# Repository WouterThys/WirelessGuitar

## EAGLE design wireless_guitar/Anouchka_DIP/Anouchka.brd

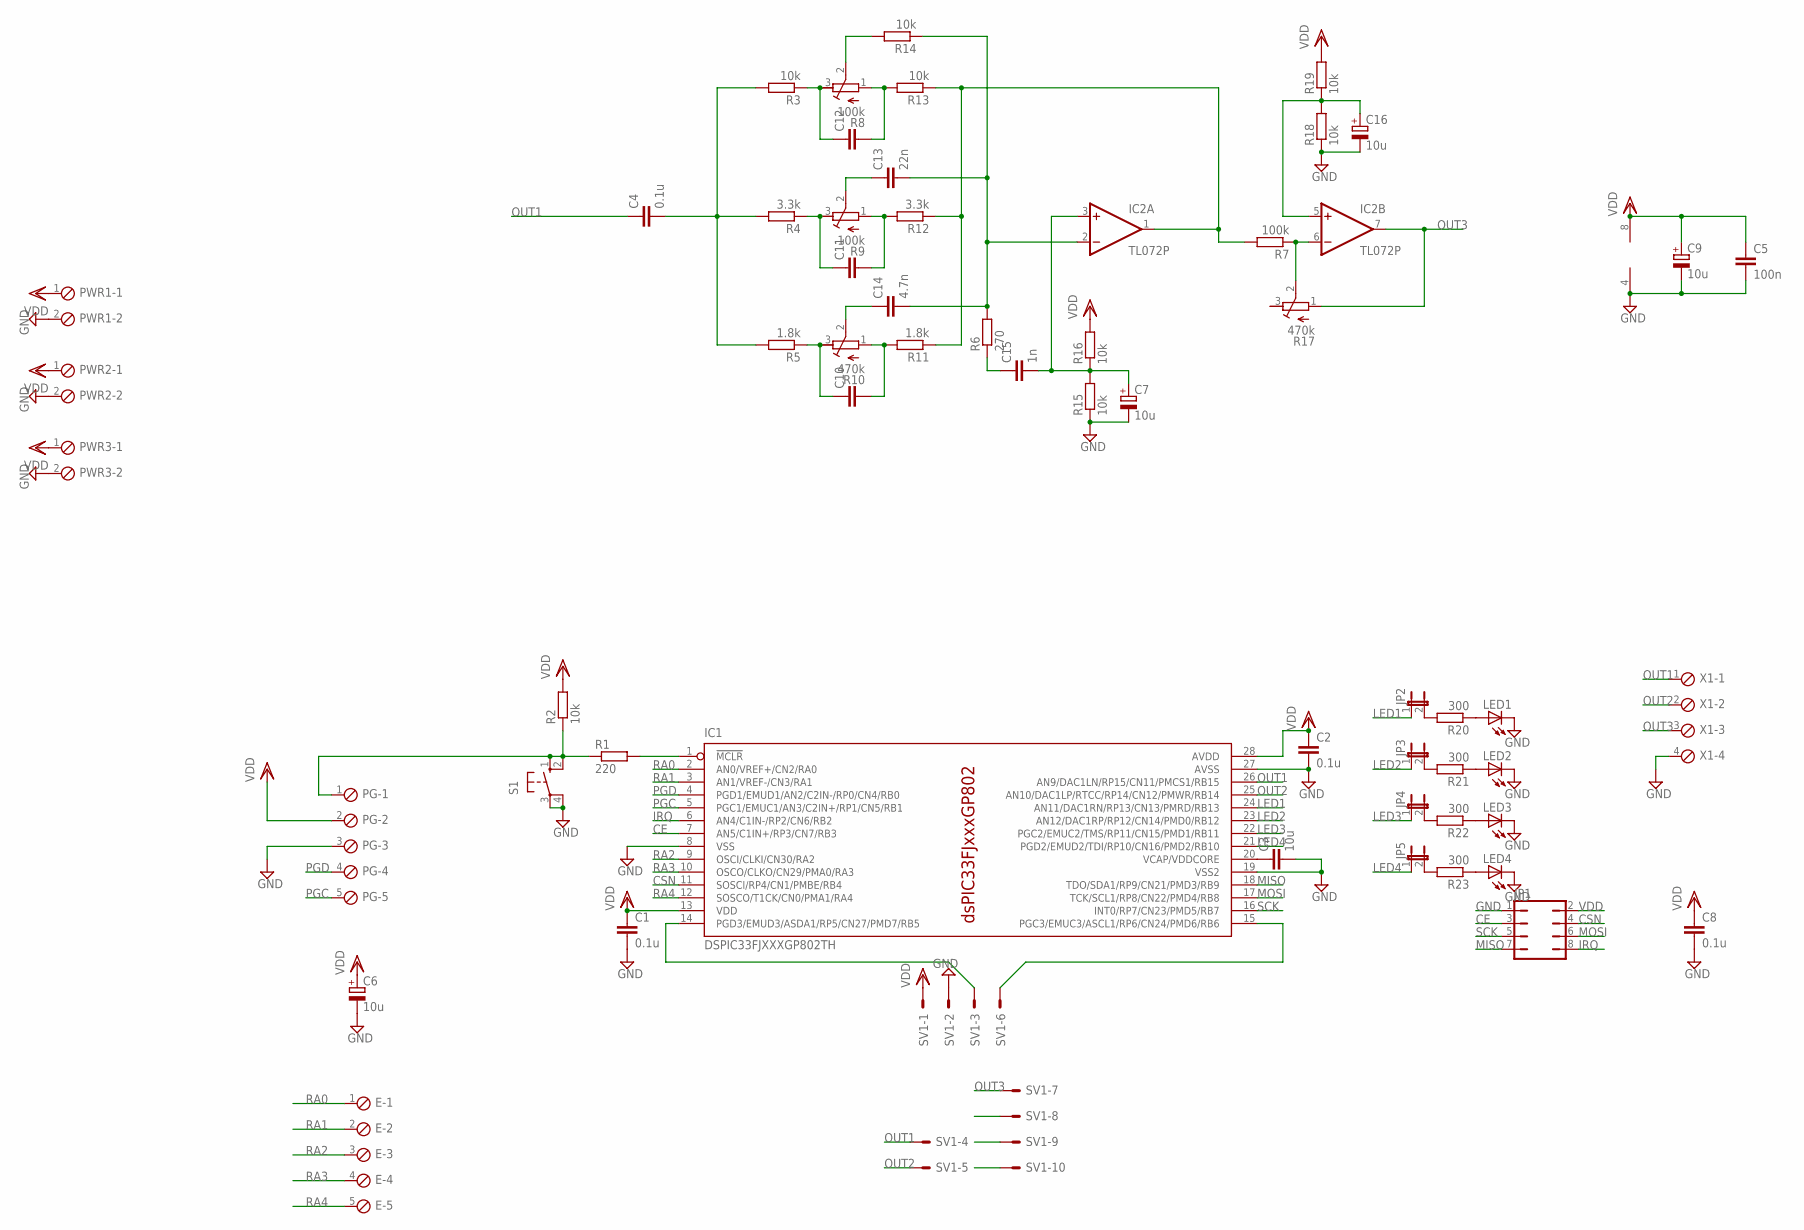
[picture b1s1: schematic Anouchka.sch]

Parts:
C1, C2, C4, C8: 0.1u; C025-024X044
C3: 10u; C025-024X044
C5: 100n; C025-024X044
C6, C7, C9, C16: 10u; E2,5-5
C10, C11, C12: C-EU025-024X044; C025-024X044
C13: 22n; C025-024X044
C14: 4.7n; C025-024X044
C15: 1n; C025-024X044
E: MPT5; 5POL254
IC1: DSPIC33FJXXXGP802TH; DIL28-3
IC2: TL072P; DIL08
JP1: JP4Q
JP2, JP3, JP4, JP5: JP1E; JP1
LED1, LED2, LED3, LED4: LED3MM
PG: MPT5; 5POL254
PWR1, PWR2, PWR3: MPT2; 2POL254
R1: 220; 0207/10
R2, R3, R13, R14, R15, R16, R18, R19: 10k; 0207/10
R4, R12: 3.3k; 0207/10
R5, R11: 1.8k; 0207/10
R6: 270; 0207/10
R7: 100k; 0207/10
R8, R9: 100k; RTRIM3339P
R10, R17: 470k; RTRIM3339P
R20, R21, R22, R23: 300; 0207/10
S1: 10-XX; B3F-10XX
SV1: ML10E; ML10
X1: MPT4; 4POL254

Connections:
CE: IC1.7 (AN5/C1IN+/RP3/CN7/RB3), JP1.3
CSN: IC1.11 (SOSCI/RP4/CN1/PMBE/RB4), JP1.4
GND: C1.2, C2.2, C3.2, C5.2, C6.-, C7.-, C8.2, C9.-, C16.-, IC1.8 (VSS), IC1.19 (VSS2), IC1.27 (AVSS), IC2.4 (V-), JP1.1, LED1.K (C), LED2.K (C), LED3.K (C), LED4.K (C), PG.3, PWR1.2, PWR2.2, PWR3.2, R15.1, R18.1, S1.3, S1.4 (P1), SV1.2, X1.4
IRQ: IC1.6 (AN4/C1IN-/RP2/CN6/RB2), JP1.8
LED1: IC1.24 (AN11/DAC1RN/RP13/CN13/PMRD/RB13), JP2.1
LED2: IC1.23 (AN12/DAC1RP/RP12/CN14/PMD0/RB12), JP3.1
LED3: IC1.22 (PGC2/EMUC2/TMS/RP11/CN15/PMD1/RB11), JP4.1
LED4: IC1.21 (PGD2/EMUD2/TDI/RP10/CN16/PMD2/RB10), JP5.1
MISO: IC1.18 (TDO/SDA1/RP9/CN21/PMD3/RB9), JP1.7
MOSI: IC1.17 (TCK/SCL1/RP8/CN22/PMD4/RB8), JP1.6
unnamed: IC1.1 (!MCLR), R1.2
unnamed: PG.1, R1.1, R2.1, S1.1 (S), S1.2 (S1)
unnamed: C3.1, IC1.20 (VCAP/VDDCORE)
unnamed: IC2.1 (OUT), R7.2, R11.1, R12.1, R13.1
unnamed: C4.2, R3.2, R4.2, R5.2
unnamed: C12.1, R3.1, R8.3 (E)
unnamed: C12.2, R8.1 (A), R13.2
unnamed: C11.1, R4.1, R9.3 (E)
unnamed: C11.2, R9.1 (A), R12.2
unnamed: C10.1, R5.1, R10.3 (E)
unnamed: C10.2, R10.1 (A), R11.2
unnamed: C14.1, R10.2 (S)
unnamed: C13.1, R9.2 (S)
unnamed: R8.2 (S), R14.2
unnamed: C13.2, C14.2, IC2.2 (-IN), R6.2, R14.1
unnamed: C15.1, R6.1
unnamed: IC2.6 (-IN), R7.1, R17.2 (S)
unnamed: C7.+, C15.2, IC2.3 (+IN), R15.2, R16.1
unnamed: C16.+, IC2.5 (+IN), R18.2, R19.1
unnamed: IC1.15 (PGC3/EMUC3/ASCL1/RP6/CN24/PMD6/RB6), SV1.6
unnamed: IC1.14 (PGD3/EMUD3/ASDA1/RP5/CN27/PMD7/RB5), SV1.3
unnamed: JP2.2, R20.2
unnamed: JP3.2, R21.2
unnamed: JP4.2, R22.2
unnamed: JP5.2, R23.2
unnamed: LED1.A, R20.1
unnamed: LED2.A, R21.1
unnamed: LED3.A, R22.1
unnamed: LED4.A, R23.1
OUT1: C4.1, IC1.26 (AN9/DAC1LN/RP15/CN11/PMCS1/RB15), SV1.4, X1.1
OUT2: IC1.25 (AN10/DAC1LP/RTCC/RP14/CN12/PMWR/RB14), SV1.5, X1.2
OUT3: IC2.7 (OUT), R17.1 (A), SV1.7, X1.3
PGC: IC1.5 (PGC1/EMUC1/AN3/C2IN+/RP1/CN5/RB1), PG.5
PGD: IC1.4 (PGD1/EMUD1/AN2/C2IN-/RP0/CN4/RB0), PG.4
RA0: E.1, IC1.2 (AN0/VREF+/CN2/RA0)
RA1: E.2, IC1.3 (AN1/VREF-/CN3/RA1)
RA2: E.3, IC1.9 (OSCI/CLKI/CN30/RA2)
RA3: E.4, IC1.10 (OSCO/CLKO/CN29/PMA0/RA3)
RA4: E.5, IC1.12 (SOSCO/T1CK/CN0/PMA1/RA4)
SCK: IC1.16 (INT0/RP7/CN23/PMD5/RB7), JP1.5
VDD: C1.1, C2.1, C5.1, C6.+, C8.1, C9.+, IC1.13 (VDD), IC1.28 (AVDD), IC2.8 (V+), JP1.2, PG.2, PWR1.1, PWR2.1, PWR3.1, R2.2, R16.2, R19.2, SV1.1

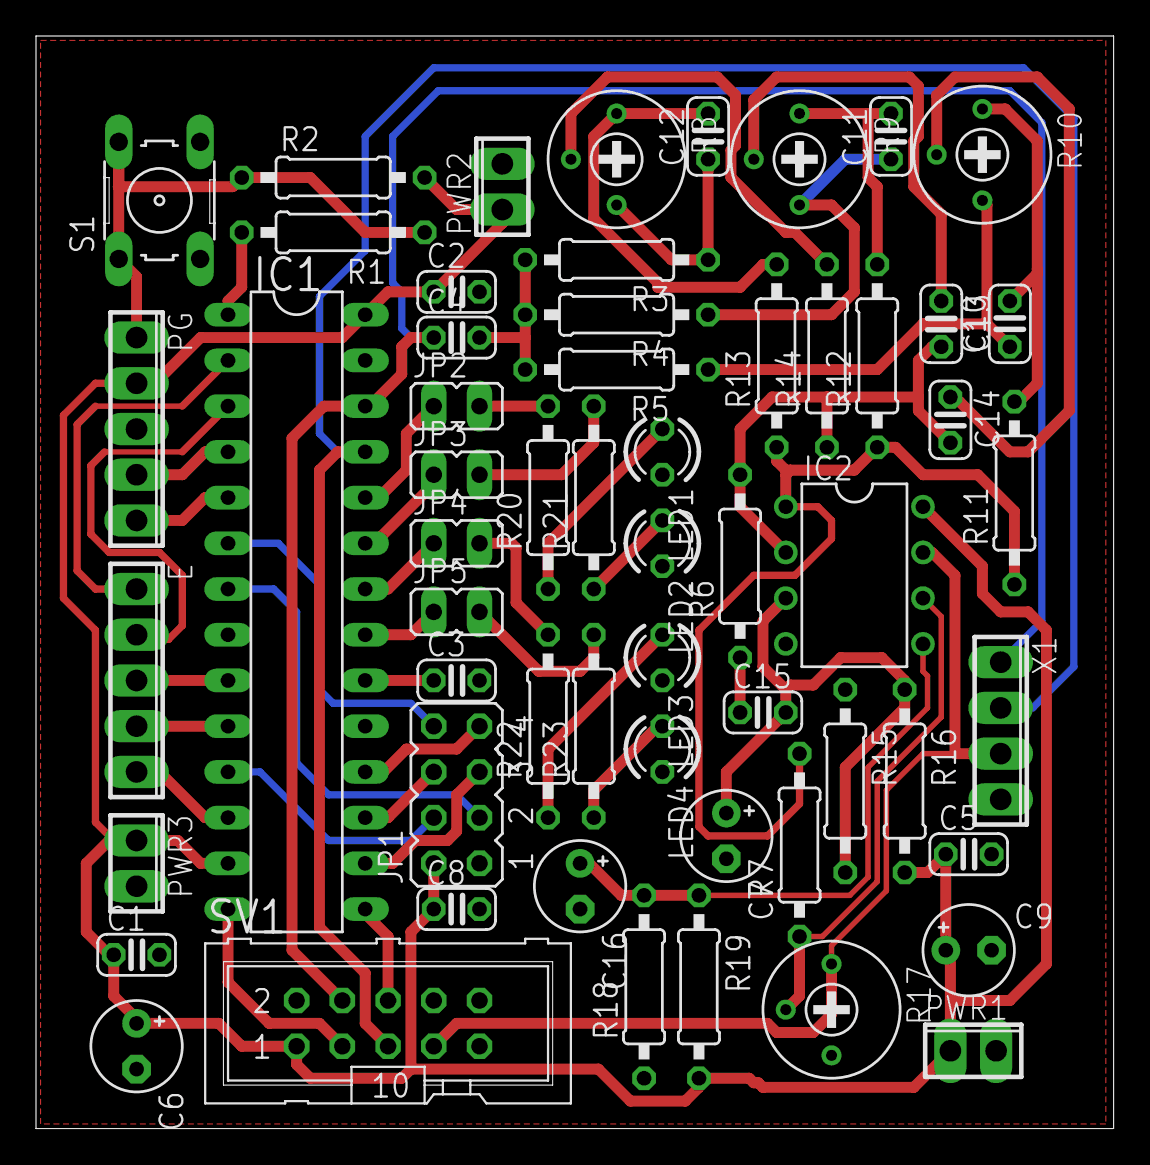
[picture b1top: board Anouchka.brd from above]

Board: 2 copper layers, 59.9 x 60.7 mm, 58 parts (0 on the bottom side), 51 nets.

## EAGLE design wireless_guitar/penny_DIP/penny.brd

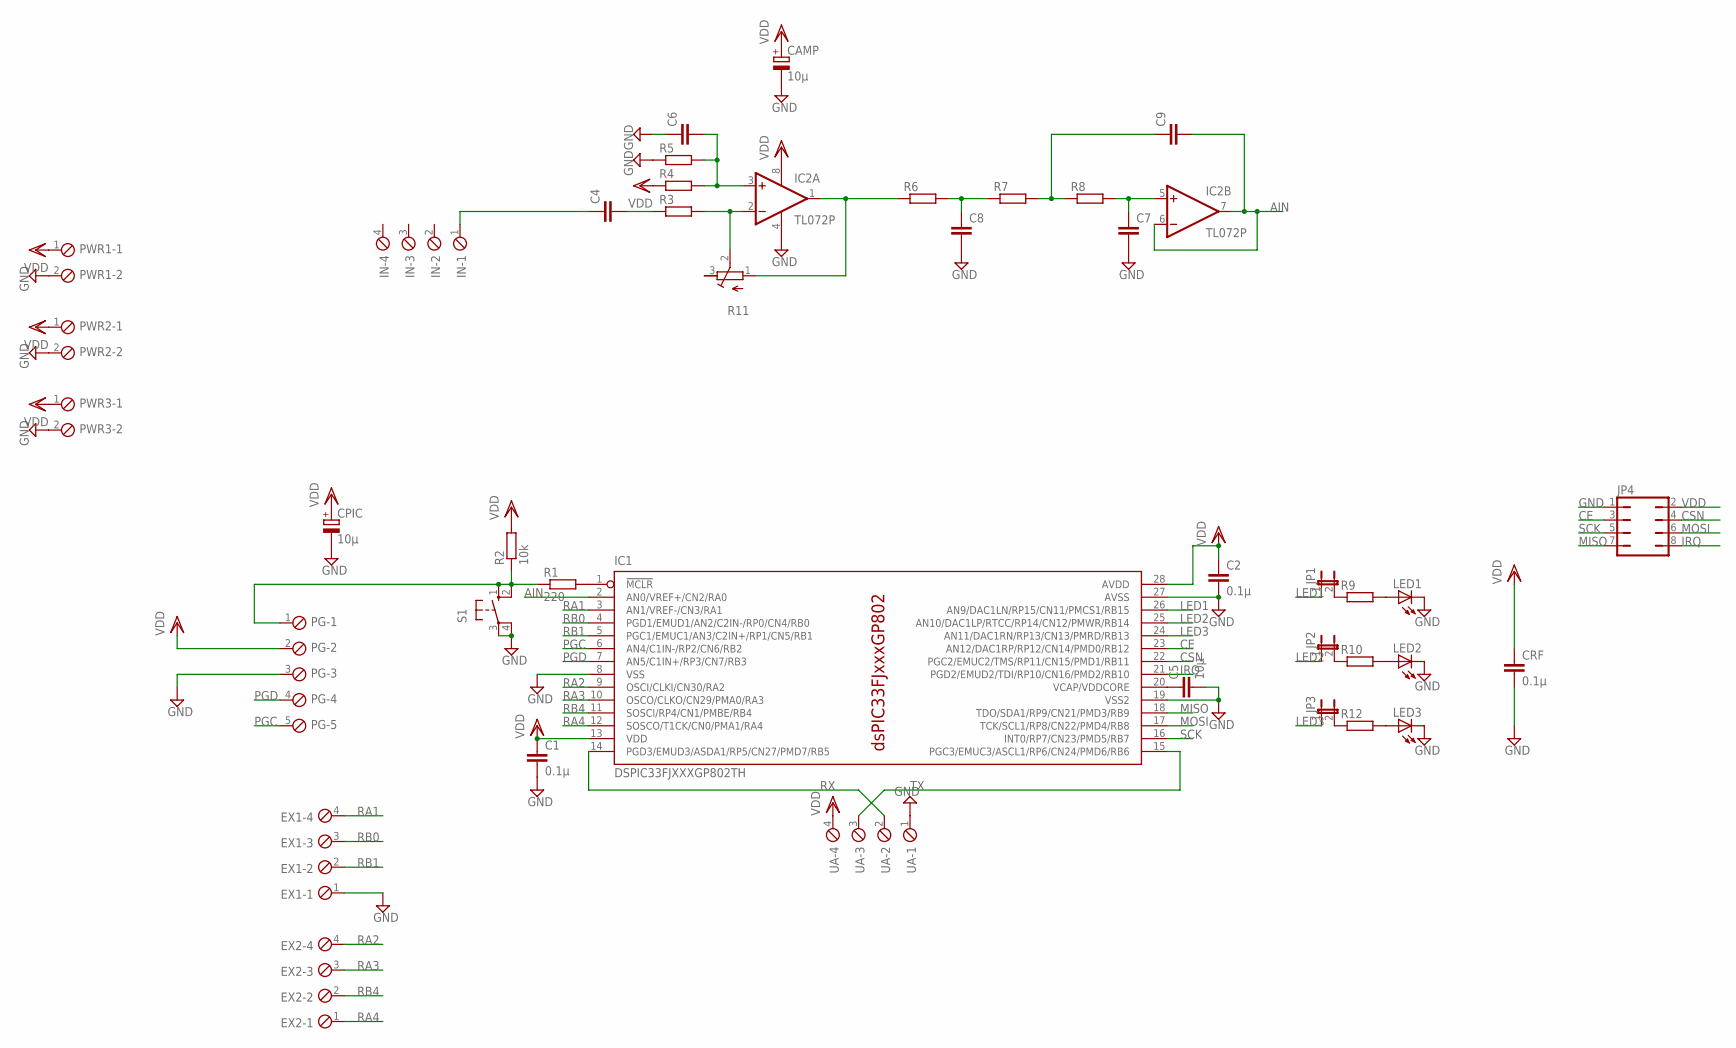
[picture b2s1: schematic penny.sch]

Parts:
C1, C2: 0.1µ; C025-024X044
C4, C6, C7, C8, C9: C-EU025-024X044; C025-024X044
C5: 10µ; C025-024X044
CAMP: 10µ; E2,5-5
CPIC: 10µ; E2,5-5
CRF: 0.1µ; C025-024X044
EX1, EX2: MPT4; 4POL254
IC1: DSPIC33FJXXXGP802TH; DIL28-3
IC2: TL072P; DIL08
IN: MPT4; 4POL254
JP1, JP2, JP3: JP1E; JP1
JP4: JP4Q
LED1, LED2, LED3: LED3MM
PG: MPT5; 5POL254
PWR1, PWR2, PWR3: MPT2; 2POL254
R1: 220; 0207/10
R2: 10k; 0207/10
R3, R4, R5, R6, R7, R8, R9, R10, R12: R-EU_0207/10; 0207/10
R11: R-TRIMM3339P; RTRIM3339P
S1: 10-XX; B3F-10XX
UA: MPT4; 4POL254

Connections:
AIN: C9.2, IC1.2 (AN0/VREF+/CN2/RA0), IC2.6 (-IN), IC2.7 (OUT)
CE: IC1.23 (AN12/DAC1RP/RP12/CN14/PMD0/RB12), JP4.3
CSN: IC1.22 (PGC2/EMUC2/TMS/RP11/CN15/PMD1/RB11), JP4.4
GND: C1.2, C2.2, C5.2, C6.1, C7.2, C8.2, CAMP.-, CPIC.-, CRF.2, EX1.1, IC1.8 (VSS), IC1.19 (VSS2), IC1.27 (AVSS), IC2.4 (V-), JP4.1, LED1.K (C), LED2.K (C), LED3.K (C), PG.3, PWR1.2, PWR2.2, PWR3.2, R5.1, S1.3, S1.4 (P1), UA.1
IRQ: IC1.21 (PGD2/EMUD2/TDI/RP10/CN16/PMD2/RB10), JP4.8
LED1: IC1.26 (AN9/DAC1LN/RP15/CN11/PMCS1/RB15), JP1.1
LED2: IC1.25 (AN10/DAC1LP/RTCC/RP14/CN12/PMWR/RB14), JP2.1
LED3: IC1.24 (AN11/DAC1RN/RP13/CN13/PMRD/RB13), JP3.1
MISO: IC1.18 (TDO/SDA1/RP9/CN21/PMD3/RB9), JP4.7
MOSI: IC1.17 (TCK/SCL1/RP8/CN22/PMD4/RB8), JP4.6
unnamed: IC1.1 (!MCLR), R1.2
unnamed: PG.1, R1.1, R2.1, S1.1 (S), S1.2 (S1)
unnamed: C6.2, IC2.3 (+IN), R4.2, R5.2
unnamed: IC2.2 (-IN), R3.2, R11.2 (S)
unnamed: C4.2, R3.1
unnamed: IC2.1 (OUT), R6.1, R11.1 (A)
unnamed: C4.1, IN.1
unnamed: C8.1, R6.2, R7.1
unnamed: C5.1, IC1.20 (VCAP/VDDCORE)
unnamed: C9.1, R7.2, R8.1
unnamed: C7.1, IC2.5 (+IN), R8.2
unnamed: JP1.2, R9.1
unnamed: LED1.A, R9.2
unnamed: JP2.2, R10.1
unnamed: LED2.A, R10.2
unnamed: LED3.A, R12.2
unnamed: JP3.2, R12.1
PGC: IC1.6 (AN4/C1IN-/RP2/CN6/RB2), PG.5
PGD: IC1.7 (AN5/C1IN+/RP3/CN7/RB3), PG.4
RA1: EX1.4, IC1.3 (AN1/VREF-/CN3/RA1)
RA2: EX2.4, IC1.9 (OSCI/CLKI/CN30/RA2)
RA3: EX2.3, IC1.10 (OSCO/CLKO/CN29/PMA0/RA3)
RA4: EX2.1, IC1.12 (SOSCO/T1CK/CN0/PMA1/RA4)
RB0: EX1.3, IC1.4 (PGD1/EMUD1/AN2/C2IN-/RP0/CN4/RB0)
RB1: EX1.2, IC1.5 (PGC1/EMUC1/AN3/C2IN+/RP1/CN5/RB1)
RB4: EX2.2, IC1.11 (SOSCI/RP4/CN1/PMBE/RB4)
RX: IC1.14 (PGD3/EMUD3/ASDA1/RP5/CN27/PMD7/RB5), UA.2
SCK: IC1.16 (INT0/RP7/CN23/PMD5/RB7), JP4.5
TX: IC1.15 (PGC3/EMUC3/ASCL1/RP6/CN24/PMD6/RB6), UA.3
VDD: C1.1, C2.1, CAMP.+, CPIC.+, CRF.1, IC1.13 (VDD), IC1.28 (AVDD), IC2.8 (V+), JP4.2, PG.2, PWR1.1, PWR2.1, PWR3.1, R2.2, R4.1, UA.4

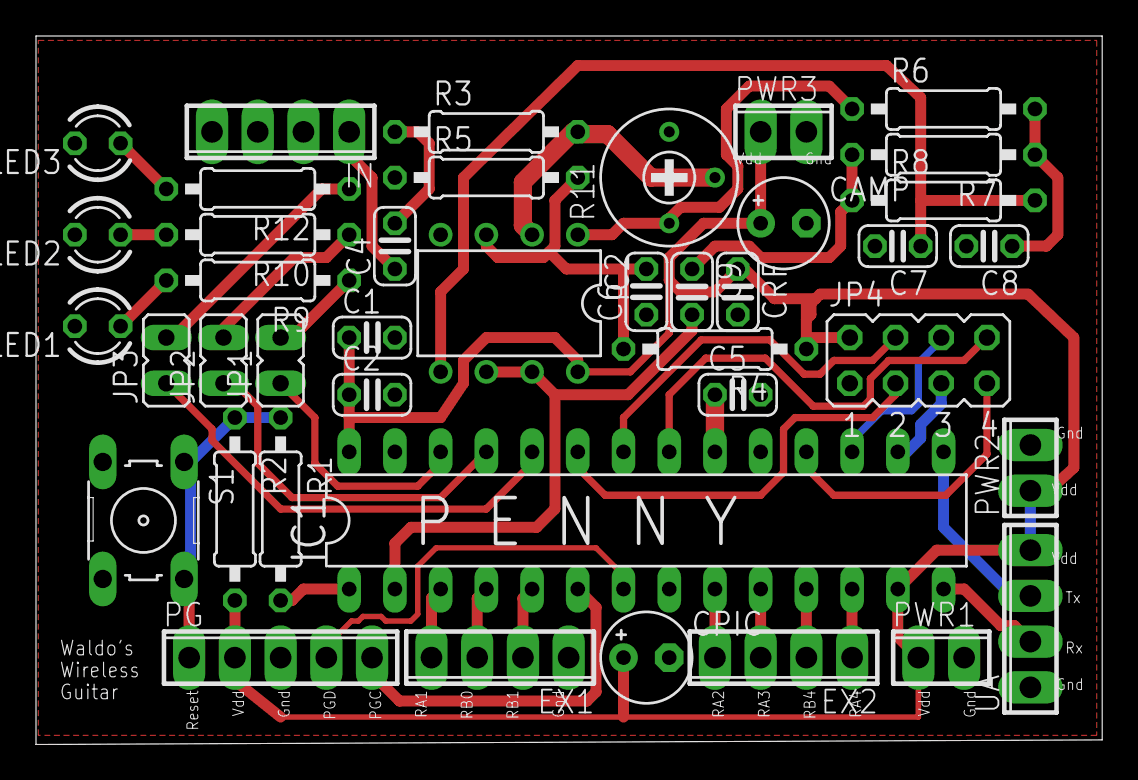
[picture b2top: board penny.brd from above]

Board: 2 copper layers, 59.2 x 39.4 mm, 41 parts (0 on the bottom side), 40 nets.

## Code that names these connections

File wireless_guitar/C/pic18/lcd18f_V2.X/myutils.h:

/* 
 * File:   myutils.h
 * Author: Avinash
 *
 * Created on 6 June, 2013, 12:30 PM
 */

#ifndef MYUTILS_H
#define	MYUTILS_H

#ifdef	__cplusplus
extern "C" {
#endif

// Hardware defines
#define BUTTON_DOWN !PORTBbits.RB0
#define BUTTON_BACK !PORTBbits.RB1
#define BUTTON_UP   !PORTBbits.RB2
#define BUTTON_OK   !PORTBbits.RB3

#define INP_B_DOWN  0x01
#define INP_B_UP    0x02
#define INP_B_OK    0x04
#define INP_B_BACK  0x08
#define INP_RX_FLAG 0x10

#define LCD_UPDATE() lcd_update()
#define INP_BUTTON_CLEAR() (inputs &= 0x10)
#define INP_UART_CLEAR() (inputs &= 0x0F)


extern void lcd_main_menu_fsm(unsigned char mmOld);
extern void lcd_sub_menu_tetten(void);
extern void lcd_sub_menu_lcd(void);
extern void lcd_sub_menu_metronoom(void);
extern void lcd_update(void);
extern void lcd_time_out(unsigned char mmOld);
extern void lcd_start_up(void);
extern void lcd_screensaver(void);
extern void lcd_connection(void);
extern void _delay_10ms(int length);

extern unsigned char i, j,first, scrs, scrs_cnt, scrs_speed,brightness;
extern unsigned char read_data, new_data, inputs, go_back;

lcd_fsm_state fsm_new_state, fsm_old_state = lINIT;
#define STATE_NEW_STATE(new_state){\
fsm_new_state = new_state;\
lcd_update();\
}

main_menu_state main_menu_old, main_menu_new = mmMENU;
#define mmSTATE_NEW_STATE(new_state){\
main_menu_new = new_state;\
lcd_update();\
}

sub_menu_lcd_state sub_menu_lcd = smBRIGHTNESS;
sub_menu_metronoom_state sub_menu_metronoom = smM1;

#ifdef	__cplusplus
}
#endif

#endif	/* MYUTILS_H */

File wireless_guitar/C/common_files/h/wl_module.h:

#ifndef _WL_MODULE_H_
#define _WL_MODULE_H_

#include <xc.h>
#include "nRF24L01.h"

// WL-Module settings
#define nrf_CH			3   // (2400 + nrf_CH)Mhz +
#define nrf_RF_DR_HIGH          0   //0 = 1Mbps, 1 = 2Mpbs
#define nrf_RF_SETUP		(RF_SETUP_RF_PWR_0 | RF_SETUP_RF_DR_1000)     // Output power 0dBm, 1Mbps
#define nrf_CONFIG_TX		((1<<MASK_RX_DR) | (1<<EN_CRC) | (1<<CRCO)) // Mask the interrupt, enable 2byte crc, PTX
#define nrf_CONFIG_RX		((1<<MASK_TX_DS) | (1<<EN_CRC) | (1<<CRCO)) // Mask the interrupt, enable 2byte crc, PRX
#define nrf_ENAA_P5             EN_AA_ENAA_P5
#define nrf_ENAA_P4             EN_AA_ENAA_P4
#define nrf_ENAA_P3             EN_AA_ENAA_P3
#define nrf_ENAA_P2             EN_AA_ENAA_P2
#define nrf_ENAA_P1             EN_AA_ENAA_P1
#define nrf_ENAA_P0             EN_AA_ENAA_P0
#define nrf_ENAA_NONE           EN_AA_ENAA_NONE
#define nrf_TX_NR_0		0
#define nrf_TX_NR_1		1
#define nrf_TX_NR_2		2
#define nrf_TX_NR_3		3
#define nrf_TX_NR_4		4
#define nrf_TX_NR_5		5
#define nrf_STATUS              ((1<<RX_DR) | (1<<TX_DS) | (1<<MAX_RT))    // Write 1 to clear

// Pin definitions for chip select and chip enabled of the wl-module
#define CE  LATB4 // RB4
#define CSN LATB3 // RB3
#define IRQ LATB2 // RB2

// Definitions for selecting and enabling wl_module module
#define nrf_CSN_H     LATBbits.CSN = 1;
#define nrf_CSN_L     LATBbits.CSN = 0;
#define nrf_CE_H      LATBbits.CE = 1;
#define nrf_CE_L      LATBbits.CE = 0;

// Defines for setting the wl_module registers for transmitting or receiving mode
/**
 * Power up the transmitter, keep CONFIG register as initialised
 */
#define TX_POWERUP nrf_config_register(CONFIG, nrf_CONFIG_TX | ( (1<<PWR_UP) | (0<<PRIM_RX) ) )

/**
 * Power up the receiver, keep CONFIG register as initialised
 */
#define RX_POWERUP nrf_config_register(CONFIG, nrf_CONFIG_RX | ( (1<<PWR_UP) | (1<<PRIM_RX) ) )

/**
 * Power Down the transmitter, keep CONFIG register as initialised
 */
#define TX_POWERDOWN nrf_config_register(CONFIG, nrf_CONFIG_TX | ( (0<<PWR_UP) | (0<<PRIM_RX) ) )

/**
 * Power Down the receiver, keep CONFIG register as initialised
 */
#define RX_POWERDOWN nrf_config_register(CONFIG, nrf_CONFIG_RX | ( (0<<PWR_UP) | (1<<PRIM_RX) ) )

// Public standard functions

/**
 * Initialize the nfr module
 * Initializes pins and interrupt to communicate with the wl_module
 * Should be called in the early initializing phase at startup.
 */
extern void nrf_init(void);

/**
 * Configure the nfr module as transmitter
 * Sets the wl-module as one of the six senders.
 * Define for every sender a unique Number (wl_module_TX_NR_x) when you call this Function.
 * Each TX will get a TX-Address corresponding to the RX-Device.
 * RX_Address_Pipe_0 must be the same as the TX-Address
 * @param tx_nr set which pipe needs to be configured to send on
 */
extern void nrf_tx_config(unsigned char tx_nr);

/**
 * Configure the nfr module as receiver
 * Sets the important registers in the wl-module and powers the module
 * in receiving mode
 */
extern void nrf_rx_config(void);

/**
 * Send ONE wireless byte, make sure the payload length is also one byte
 * @param value byte to send wireless
 */
extern void nrf_send_byte(unsigned char value);

/**
 * Send ARRAY of bytes
 * @param value array to send
 * @param len length of the array, should be the same as the payload length
 */
extern void nrf_send_array(unsigned char * value, unsigned char len);

/**
 * Load the adress for receiving
 * @param adr
 */
extern void nrf_set_RADDR(unsigned char * adr);

/**
 * Load the adress for transmitting
 * @param adr
 */
extern void nrf_set_TADDR(unsigned char * adr);

/**
 * Get data array from the payload
 * @param data array to write data in
 * @return return STATUS register
 */
extern unsigned char nrf_get_data(unsigned char * data);

extern unsigned char nrf_get_data_byte(void);

/**
 * Get data array from the payload
 * @param data array to write data in
 * @return return STATUS register
 */
extern unsigned char nrf_get_data_array(unsigned char * data);


/**
 * Configure ONE nfr module register
 * Clocks only one byte into the given wl-module register
 * @param reg which register needs to be configured
 * @param value what is the value for the register
 */
extern void nrf_config_register(unsigned char reg, unsigned char value);

/**
 * Read the nfr module registers
 * Reads only one byte registers
 * @param reg register to read
 * @return value of the red register
 */
extern unsigned char nrf_read_register(unsigned char reg);

/**
 * Confige MORE nrf module registers
 * Writes an array of bytes into inte the wl-module registers.
 * @param reg register to configure
 * @param value array of bytes to write
 * @param len length of the array
 */
extern void nrf_write_register(unsigned char reg, unsigned char * value, unsigned char len);

#endif /* _SETUP_NRF24L01_H_ */
